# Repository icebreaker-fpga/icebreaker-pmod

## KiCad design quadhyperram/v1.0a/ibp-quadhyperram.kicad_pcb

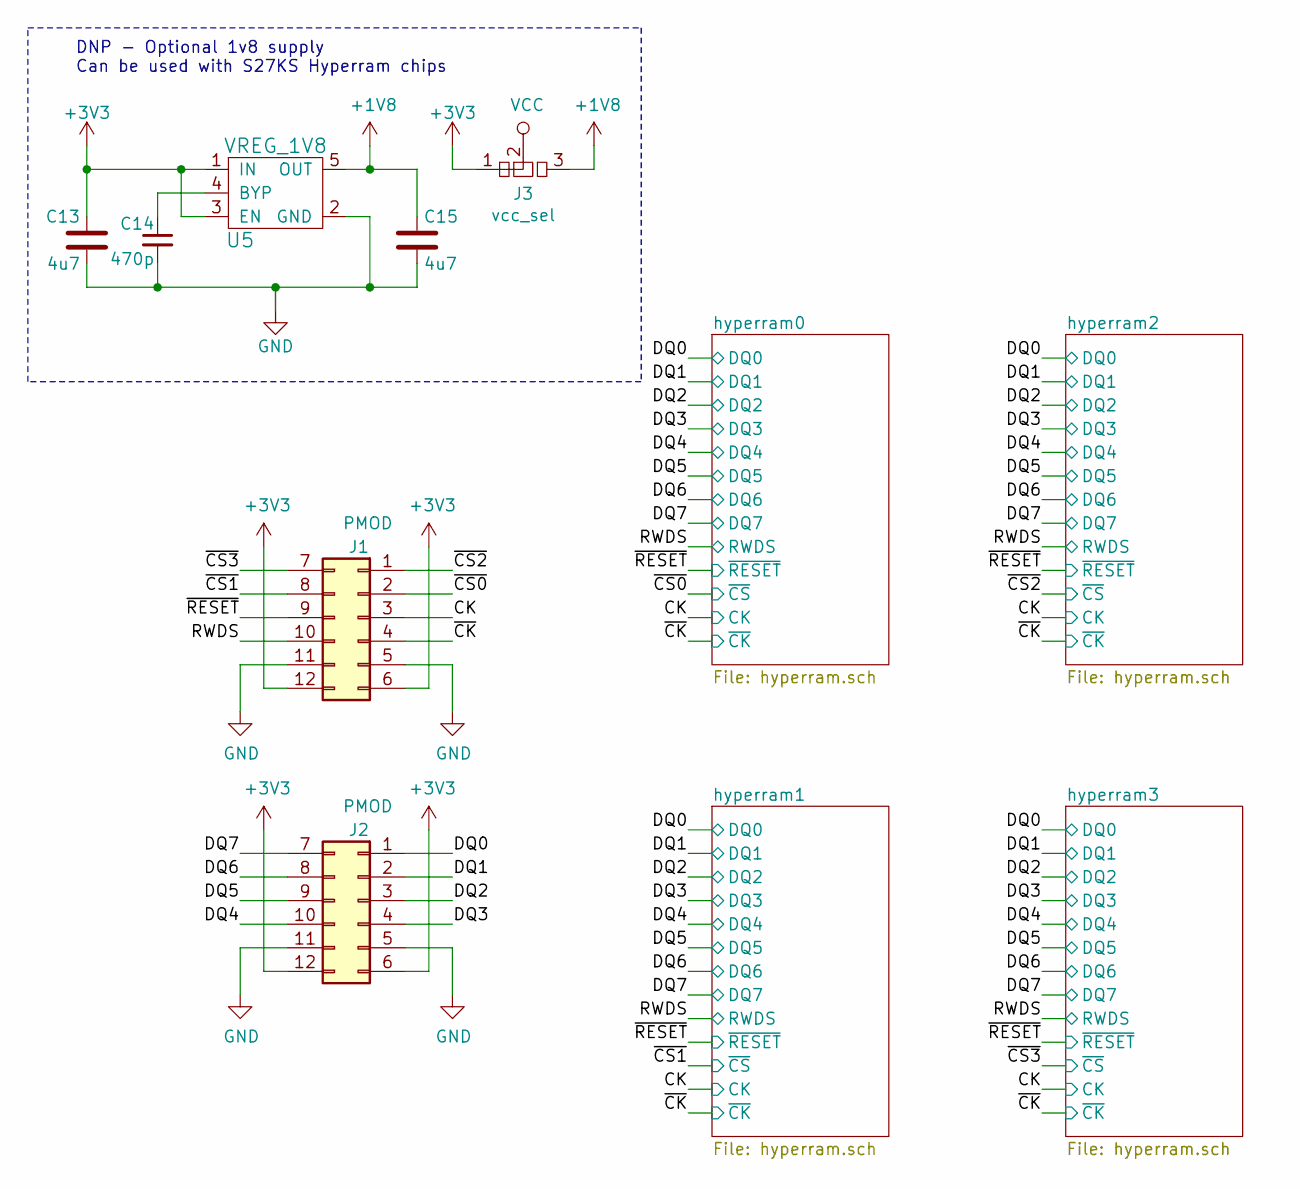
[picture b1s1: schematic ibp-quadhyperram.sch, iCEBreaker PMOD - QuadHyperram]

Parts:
C13, C15: 4u7; C_0603
C14: 470p; C_0402
J1, J2: PMOD; PMODHeader_2x06_P2.54mm_Horizontal
J3: vcc_sel; J_NCNO_0903_30
U5: VREG_1V8; SOT-23-5

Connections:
+1V8: C15.1, J3.3, U5.5 (OUT)
+3V3: C13.1, J1.6, J1.12, J2.6, J2.12, J3.1, U5.1 (IN), U5.3 (EN)
/CK: J1.3; also elsewhere on the board
/DQ0: J2.1; also elsewhere on the board
/DQ1: J2.2; also elsewhere on the board
/DQ2: J2.3; also elsewhere on the board
/DQ3: J2.4; also elsewhere on the board
/DQ4: J2.10; also elsewhere on the board
/DQ5: J2.9; also elsewhere on the board
/DQ6: J2.8; also elsewhere on the board
/DQ7: J2.7; also elsewhere on the board
/RWDS: J1.10; also elsewhere on the board
/~CK: J1.4; also elsewhere on the board
/~CS0: J1.2; also elsewhere on the board
/~CS1: J1.8; also elsewhere on the board
/~CS2: J1.1; also elsewhere on the board
/~CS3: J1.7; also elsewhere on the board
/~RESET: J1.9; also elsewhere on the board
GND: C13.2, C14.2, C15.2, J1.5, J1.11, J2.5, J2.11, U5.2 (GND); also elsewhere on the board
unnamed: C14.1, U5.4 (BYP)
VCC: J3.2; also elsewhere on the board

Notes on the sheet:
DNP - Optional 1v8 supply Can be used with S27KS Hyperram chips

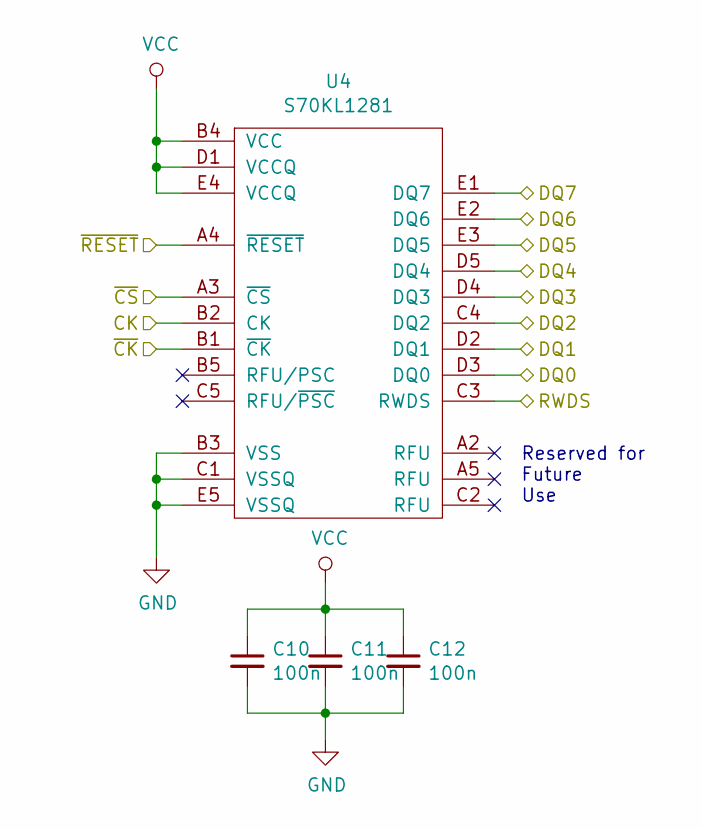
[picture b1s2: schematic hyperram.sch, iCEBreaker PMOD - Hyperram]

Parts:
C1, C2, C3: 100n; C_0402
U1: S70KL1281; BGA-24_5x5_6.0x8.0mm

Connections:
/CK: U1.B2 (CK); also elsewhere on the board
/DQ0: U1.D3 (DQ0); also elsewhere on the board
/DQ1: U1.D2 (DQ1); also elsewhere on the board
/DQ2: U1.C4 (DQ2); also elsewhere on the board
/DQ3: U1.D4 (DQ3); also elsewhere on the board
/DQ4: U1.D5 (DQ4); also elsewhere on the board
/DQ5: U1.E3 (DQ5); also elsewhere on the board
/DQ6: U1.E2 (DQ6); also elsewhere on the board
/DQ7: U1.E1 (DQ7); also elsewhere on the board
/RWDS: U1.C3 (RWDS); also elsewhere on the board
/~CK: U1.B1 (~CK); also elsewhere on the board
/~CS0: U1.A3 (~CS); also elsewhere on the board
/~RESET: U1.A4 (~RESET); also elsewhere on the board
GND: C1.2, C2.2, C3.2, U1.B3 (VSS), U1.C1 (VSSQ), U1.E5 (VSSQ); also elsewhere on the board
VCC: C1.1, C2.1, C3.1, U1.B4 (VCC), U1.D1 (VCCQ), U1.E4 (VCCQ); also elsewhere on the board

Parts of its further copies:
C4, C5, C6, C7, C8, C9, C10, C11, C12: 100n; C_0402
U2, U3, U4: S70KL1281; BGA-24_5x5_6.0x8.0mm

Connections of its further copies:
/CK: U2.B2 (CK), U3.B2 (CK), U4.B2 (CK); also elsewhere on the board
/DQ0: U2.D3 (DQ0), U3.D3 (DQ0), U4.D3 (DQ0); also elsewhere on the board
/DQ1: U2.D2 (DQ1), U3.D2 (DQ1), U4.D2 (DQ1); also elsewhere on the board
/DQ2: U2.C4 (DQ2), U3.C4 (DQ2), U4.C4 (DQ2); also elsewhere on the board
/DQ3: U2.D4 (DQ3), U3.D4 (DQ3), U4.D4 (DQ3); also elsewhere on the board
/DQ4: U2.D5 (DQ4), U3.D5 (DQ4), U4.D5 (DQ4); also elsewhere on the board
/DQ5: U2.E3 (DQ5), U3.E3 (DQ5), U4.E3 (DQ5); also elsewhere on the board
/DQ6: U2.E2 (DQ6), U3.E2 (DQ6), U4.E2 (DQ6); also elsewhere on the board
/DQ7: U2.E1 (DQ7), U3.E1 (DQ7), U4.E1 (DQ7); also elsewhere on the board
/RWDS: U2.C3 (RWDS), U3.C3 (RWDS), U4.C3 (RWDS); also elsewhere on the board
/~CK: U2.B1 (~CK), U3.B1 (~CK), U4.B1 (~CK); also elsewhere on the board
/~CS1: U2.A3 (~CS); also elsewhere on the board
/~CS2: U3.A3 (~CS); also elsewhere on the board
/~CS3: U4.A3 (~CS); also elsewhere on the board
/~RESET: U2.A4 (~RESET), U3.A4 (~RESET), U4.A4 (~RESET); also elsewhere on the board
GND: C4.2, C5.2, C6.2, C7.2, C8.2, C9.2, C10.2, C11.2, C12.2, U2.B3 (VSS), U2.C1 (VSSQ), U2.E5 (VSSQ), U3.B3 (VSS), U3.C1 (VSSQ), U3.E5 (VSSQ), U4.B3 (VSS), U4.C1 (VSSQ), U4.E5 (VSSQ); also elsewhere on the board
VCC: C4.1, C5.1, C6.1, C7.1, C8.1, C9.1, C10.1, C11.1, C12.1, U2.B4 (VCC), U2.D1 (VCCQ), U2.E4 (VCCQ), U3.B4 (VCC), U3.D1 (VCCQ), U3.E4 (VCCQ), U4.B4 (VCC), U4.D1 (VCCQ), U4.E4 (VCCQ); also elsewhere on the board

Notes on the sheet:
Reserved for Future Use

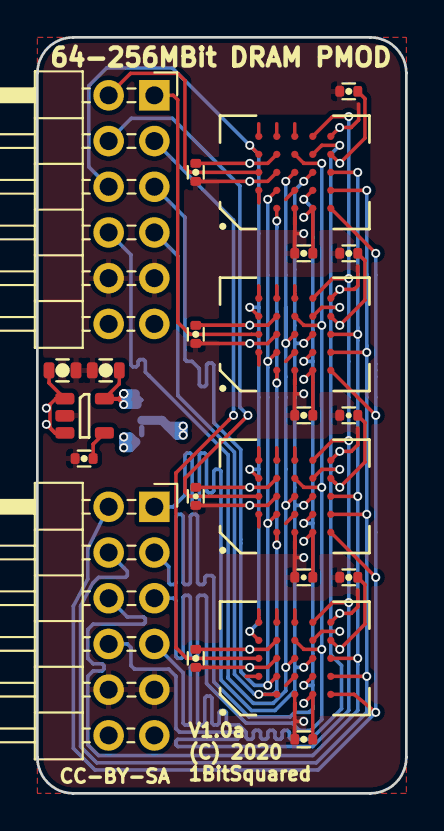
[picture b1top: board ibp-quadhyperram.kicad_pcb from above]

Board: 4 copper layers, 20.5 x 42.0 mm, 23 parts (1 on the bottom side), 21 nets.

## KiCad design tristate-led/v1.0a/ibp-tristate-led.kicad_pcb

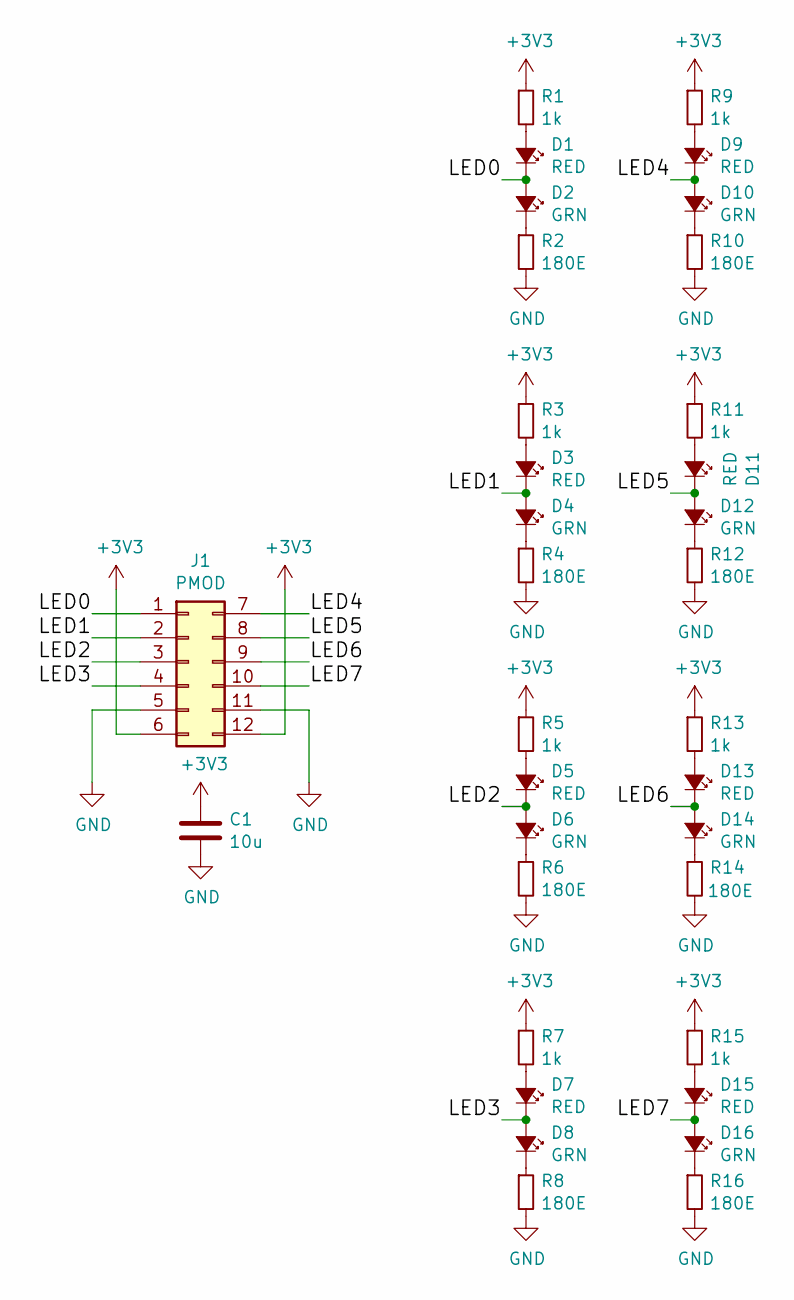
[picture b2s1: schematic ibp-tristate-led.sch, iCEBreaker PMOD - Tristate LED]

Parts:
C1: 10u; C_0603
D1, D3, D5, D7, D9, D11, D13, D15: RED; D_0603
D2, D4, D6, D8, D10, D12, D14, D16: GRN; D_0603
J1: PMOD; PMODHeader_2x06_P2.54mm_Horizontal
R1, R3, R5, R7, R9, R11, R13, R15: 1k; R_0402
R2, R4, R6, R8, R10, R12, R14, R16: 180E; R_0402

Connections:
+3V3: C1.1, J1.6, J1.12, R1.1, R3.1, R5.1, R7.1, R9.1, R11.1, R13.1, R15.1
/LED0: D1.C, D2.A, J1.1
/LED1: D3.C, D4.A, J1.2
/LED2: D5.C, D6.A, J1.3
/LED3: D7.C, D8.A, J1.4
/LED4: D9.C, D10.A, J1.7
/LED5: D11.C, D12.A, J1.8
/LED6: D13.C, D14.A, J1.9
/LED7: D15.C, D16.A, J1.10
GND: C1.2, J1.5, J1.11, R2.2, R4.2, R6.2, R8.2, R10.2, R12.2, R14.2, R16.2
unnamed: D1.A, R1.2
unnamed: D2.C, R2.1
unnamed: D3.A, R3.2
unnamed: D4.C, R4.1
unnamed: D5.A, R5.2
unnamed: D6.C, R6.1
unnamed: D7.A, R7.2
unnamed: D8.C, R8.1
unnamed: D9.A, R9.2
unnamed: D10.C, R10.1
unnamed: D11.A, R11.2
unnamed: D12.C, R12.1
unnamed: D13.A, R13.2
unnamed: D14.C, R14.1
unnamed: D15.A, R15.2
unnamed: D16.C, R16.1

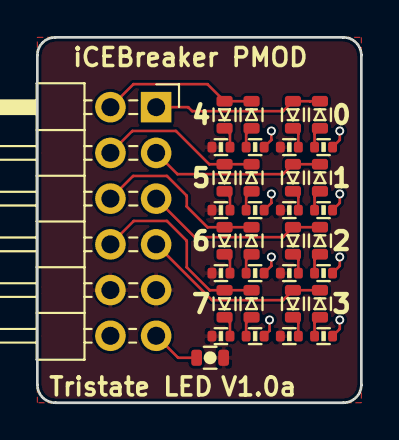
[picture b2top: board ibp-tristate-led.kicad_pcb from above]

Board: 2 copper layers, 18.0 x 20.3 mm, 34 parts (0 on the bottom side), 26 nets.

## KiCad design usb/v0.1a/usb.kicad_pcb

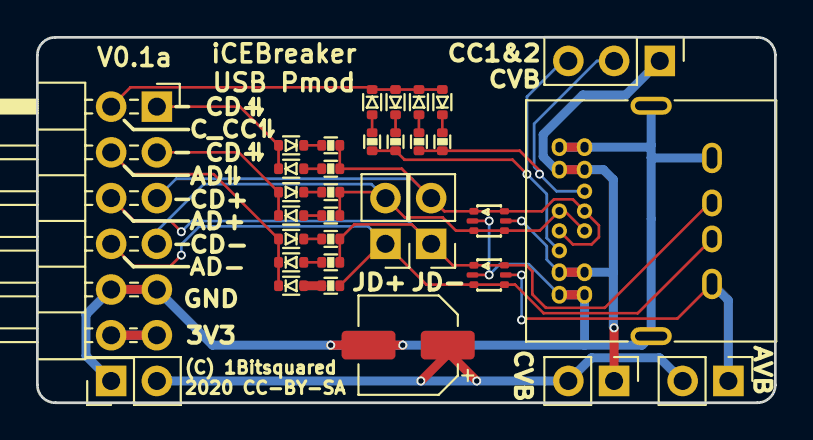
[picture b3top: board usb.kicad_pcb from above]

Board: 2 copper layers, 41.0 x 20.3 mm, 33 parts (0 on the bottom side), 25 nets.

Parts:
C1: DNP; CP_Elec_5x3.9
D1, D2, D3, D4, D5, D6, D7, D8, D9, D10, D11: ~~800mVf; D_SOD-523
J1: PMOD; PMODHeader_2x06_P2.54mm_Horizontal
J2: USB_AC_Combo_Receptacle_USB2.0; USB_A_C_Receptacle_AdamTech_USB-C31-A-D-VT-CS1
J3: USBC_CC; PinHeader_1x03_P2.54mm_Vertical
J4: JVBUSA; PinHeader_1x02_P2.54mm_Vertical
J5: JDP; PinHeader_1x02_P2.54mm_Vertical
J6: JDM; PinHeader_1x02_P2.54mm_Vertical
J7: AUX5V; PinSocket_2x01_P2.54mm_Vertical
J8: JVBUSC; PinHeader_1x02_P2.54mm_Vertical
R1, R4, R10: 1.1K; R_0402
R2, R3, R9, R11: 12K; R_0402
R5, R7: 36K; R_0402
R6, R8: 5.1K; R_0402
U1, U2: USBLC6-2; SOT-666

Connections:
+5V: C1.1, J4.2, J7.2, J8.2
/CC1: J2.A5, J3.3, R5.1, R6.1
/CC2: J2.B5, J3.2, R7.1, R8.1
/USBA_DM: J1.10, J2.2, J6.1, R2.1, U1.3, U1.4
/USBA_DP: J1.9, J2.3, J5.1, R1.1, R3.1, U1.1, U1.6
/USBA_PUPD: D1.A, D2.C, D3.C, J1.8
/USBA_VBUS: J2.1, J4.1, U1.5
/USBC_CC: D8.A, D9.C, D10.A, D11.C, J1.7
/USBC_DM: J1.4, J2.A7, J2.B7, J6.2, R10.1, R11.1, U2.3, U2.4
/USBC_DM_PUPD: D6.A, D7.C, J1.2
/USBC_DP: J1.3, J2.A6, J2.B6, J5.2, R4.1, R9.1, U2.1, U2.6
/USBC_DP_PUPD: D4.A, D5.C, J1.1
/USBC_VBUS: J2.A4, J2.A9, J2.B4, J2.B9, J3.1, J8.1, U2.5
GND: C1.2, J1.5, J1.11, J2.4, J2.A1, J2.A12, J2.B1, J2.B12, J2.S1, J2.S2, J7.1, U1.2, U2.2
unnamed: D1.C, R1.2
unnamed: D2.A, R3.2
unnamed: D3.A, R2.2
unnamed: D4.C, R4.2
unnamed: D5.A, R9.2
unnamed: D6.C, R10.2
unnamed: D7.A, R11.2
unnamed: D8.C, R5.2
unnamed: D9.A, R6.2
unnamed: D10.C, R7.2
unnamed: D11.A, R8.2

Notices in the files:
quadhyperram/v1.0a/hyperram.sch:
License: CC-BY-SA 4.0
quadhyperram/v1.0a/ibp-quadhyperram.kicad_pcb:
(C) 2020
CC-BY-SA
tristate-led/v1.0a/ibp-tristate-led.kicad_pcb:
(C) 2018 Piotr Esden-Tempski
(C) 2018 1BitSquared
License: CC-BY-SA V4.0
(C) 2018
CC-BY-SA 4.0
usb/v0.1a/usb.kicad_pcb:
(C) 2019 Piotr Esden-Tempski
(C) 2019 1BitSquared
2020 CC-BY-SA
